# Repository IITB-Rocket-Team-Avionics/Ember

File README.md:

# Ember

Ember is the SRAD flight computer system of the IITB Rocket Team, developed as an experimental platform with mitigations for issues faced by previous systems and as a testbed for new avionics architecture.

## Version Descriptions

### Ember Pilot
Proof of concept version validating new LoRa telemetry and core sensor suite. Features a Raspberry Pi Pico 2 dev board instead of a bare-metal hardware design. All systems validated for future versions.

| Parameter | Details |
|-----------|---------|
| MCU | RP2350A (Pico 2 dev board) |
| Layers | 4 |
| Sensors | BMP280, BNO055, KX134 |
| GNSS | Teseo LIV3F |
| Telemetry | Waveshare Core SX1262 (920MHz LoRa) |

---

### Ember V0.2 (Ember)
First full flight version. Flew successfully at IREC 2026, reaching an apogee of 9,463 ft with a SRAD N-class KNSB motor — 2% overshoot on OpenRocket predicted apogee of 9,272 ft. Split into two boards: Flight Computer Unit (FCU) and Telemetry & Data Unit (TDU).

| Parameter | Details |
|-----------|---------|
| FCU MCU | RP2350A (Pico 2 dev board) |
| TDU MCU | RP2350A (Pico 2 dev board) |
| Layers | 2 |
| Sensors | BMP280, BNO055, KX134, NXP MPXV5100DP |
| GNSS | Quectel L89HA (multi-constellation) |
| Telemetry | Waveshare Core1262 SX1262 (920MHz LoRa) |
| Recovery | Dual deploy — drogue at apogee, main at 400m AGL |
| Pyro channels | 4 (2 primary, 2 redundant) |
| Data logging | External flash |
| COTS backup | EasyMini V2 |

---

### Ember V1 (In Development)
Major architectural redesign with full separation of concerns across dedicated board types. Introduces triple modular redundant recovery, distributed CAN bus architecture, and significantly upgraded data acquisition.

**Board types:**

**NTDU (Navigation, Telemetry & Data Unit)** — main board. Independent sensor suite for navigation and state estimation, GNSS, LoRa telemetry, data acquisition (dp probe, strain gauges), configuration authority for all nodes on boot, aggregates and logs data from all CAN nodes.

| Parameter | Details |
|-----------|---------|
| MCU | STM32H573 |
| Sensors | BMP384, BNO055, KX134, NXP MPXV5100DP (via ADS1220), BX350-3AA strain gauges (via ADS1220) |
| GNSS | Quectel L89HA |
| Telemetry | SX1262 920MHz LoRa |
| Data logging | OctoSPI NOR flash + microSD |
| Communication | CAN bus (all nodes) |
| Power | 2S Li-ion, AP63205WU buck (5V) |

**RU (Recovery Unit) — x3** — dedicated recovery boards in triple modular redundant configuration. Distributed 2-of-3 voting via CAN bus. Each board independently detects apogee and participates in consensus voting.

| Parameter | Details |
|-----------|---------|
| MCU | STM32F411 |
| Sensors | BMP280, single-axis accelerometer |
| Pyro channels | 2 (drogue + main) |
| Communication | CAN bus (shared with NTDU) |
| RTOS | FreeRTOS |
| Power | 1S Li-ion (isolated per board) |
| Voting | 2-of-3 mid-value select consensus |

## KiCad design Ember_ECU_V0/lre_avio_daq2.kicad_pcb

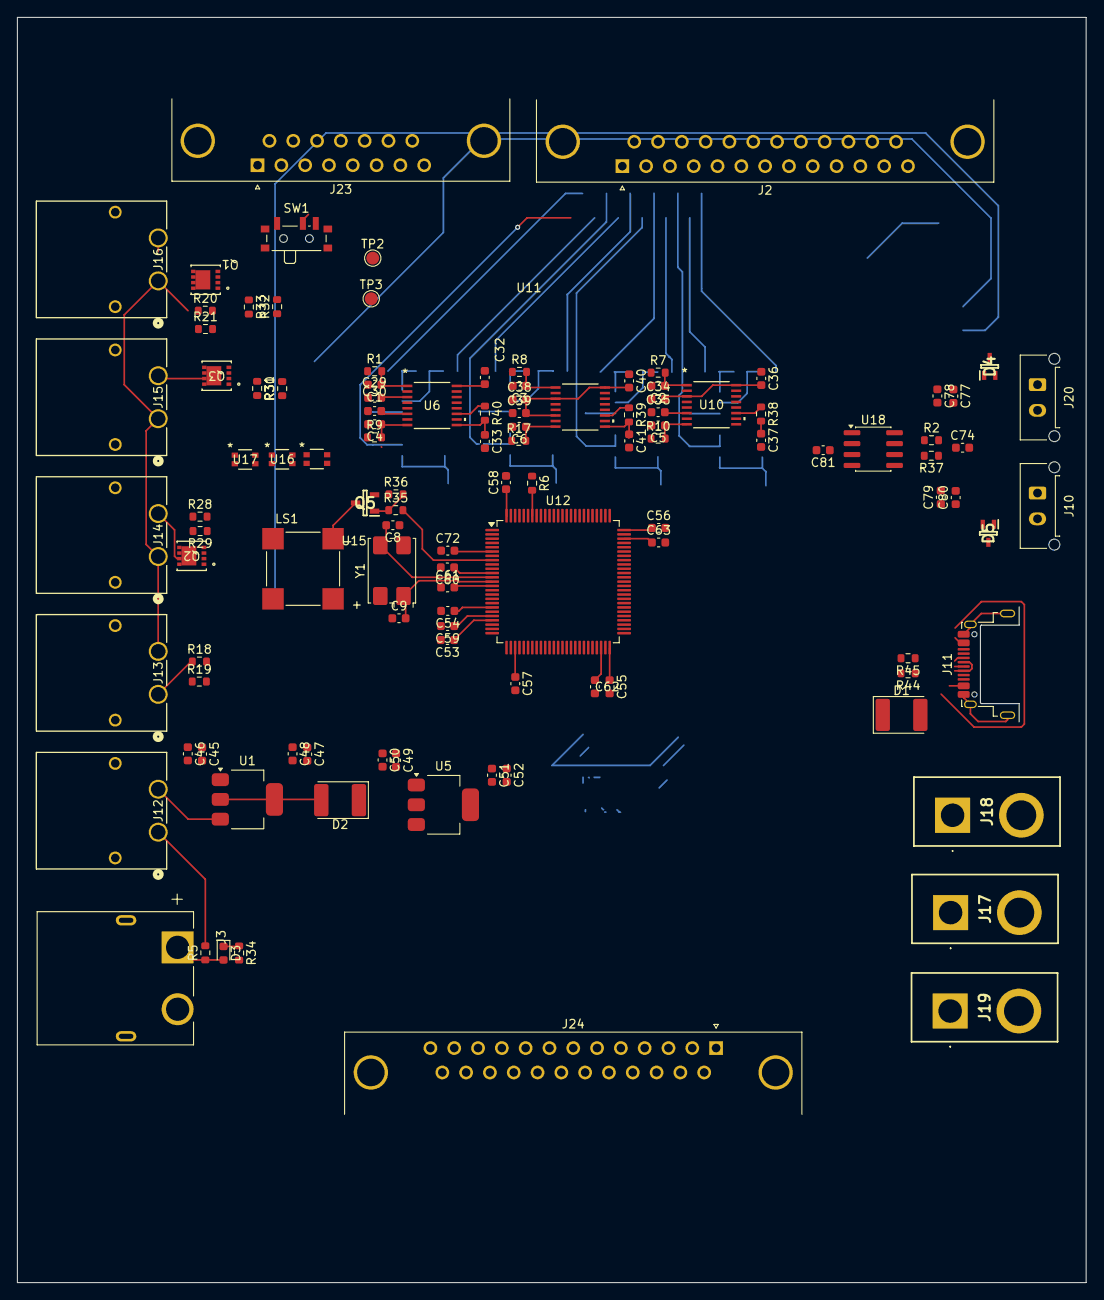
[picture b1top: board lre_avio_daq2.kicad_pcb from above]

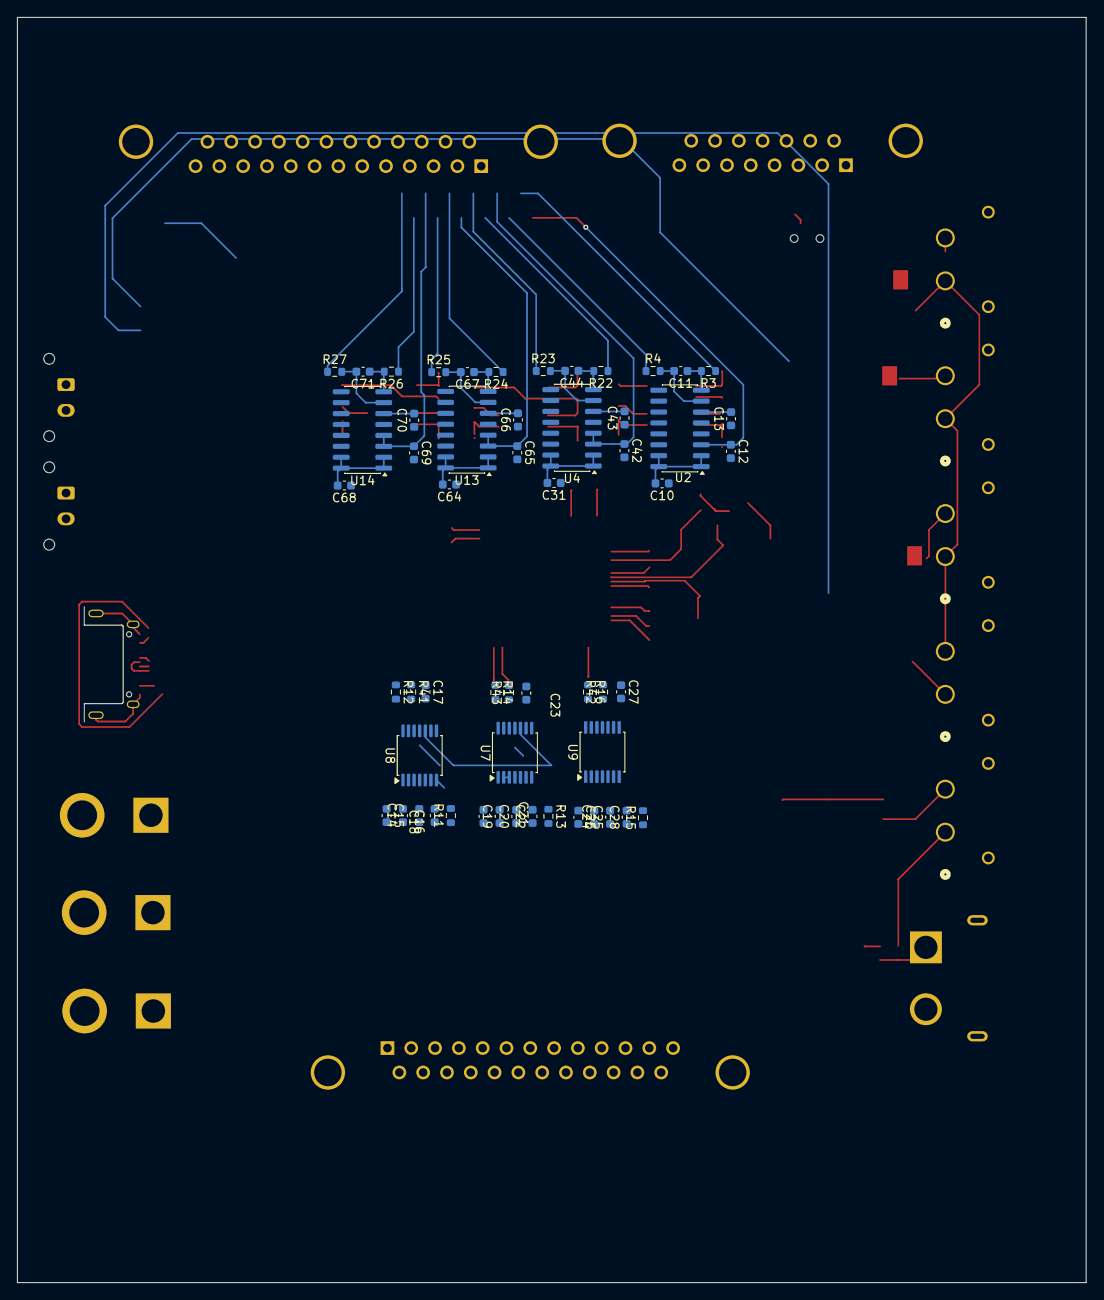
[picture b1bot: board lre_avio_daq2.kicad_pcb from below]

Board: 4 copper layers, 124.4 x 147.2 mm, 168 parts (55 on the bottom side), 125 nets.

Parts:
C1, C2, C3, C4, C5, C6: 1nF; C_0603_1608Metric
C8, C9: 20 pF; C_0603_1608Metric
C10, C12, C31, C42, C64, C65, C68, C69: 10 muF; C_0603_1608Metric
C11, C13, C14, C16, C17, C19, C22, C23, C24, C27, C28, C43, C44, C66, C67, C70, C71: 0.1 muF; C_0603_1608Metric
C15, C18, C20, C21, C25, C26: 0.01 muF; C_0603_1608Metric
C29, C30, C32, C33, C34, C35, C36, C37, C38, C39, C40, C41, C74: C; C_0603_1608Metric
C45, C47, C50, C51, C53, C54, C55, C56, C57, C58, C61, C72: 100 nF; C_0603_1608Metric
C46, C48, C49, C52, C60: 1 muF; C_0603_1608Metric
C59: 10 nF; C_0603_1608Metric
C62, C63: 4.7 muF; C_0603_1608Metric
C77, C78, C79, C80: 47pf; C_0603_1608Metric
C81: 100nF; C_0603_1608Metric
D1, D2: D_Schottky; D_2114_3652Metric
D3: LED; LED_0603_1608Metric
D4, D5: ESDCAN02-2BWY; SOT65P210X110-3N
J2, J24: DB25_Socket_MountingHoles; DSUB-25_Socket_Horizontal_P2.77x2.84mm_EdgePinOffset4.94mm_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
J3: XT60PW-M; AMASS_XT60PW-M
J10, J20: Conn_01x02_Pin; Molex_Micro-Fit_3.0_43650-0215_1x02_P3.00mm_Vertical
J11: USB_C_Receptacle_USB2.0_16P; USB_C_Receptacle_Amphenol_12401948E412A
J12, J13, J14, J15, J16: XT30PW-F; CONN_XT30PW-F_AMA
J17, J18, J19: SMPW-CC-K-M; SMPWCCKM
J23: DA15_Socket_MountingHoles; DSUB-15_Socket_Horizontal_P2.77x2.84mm_EdgePinOffset4.94mm_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
LS1: CMT-8530S-SMT; CUI_CMT-8530S-SMT
Q1, Q2, Q3: SISA96DN-T1-GE3; MOSFET_1DN-T1-GE3_VIS
Q5: SOT95P240X115-3N
R1, R3, R4, R7, R8, R9, R10, R17, R22, R23, R24, R25, R26, R27, R35: 100; R_0603_1608Metric
R2, R34, R37: R; R_0603_1608Metric
R5: RSX501LAM20TR; R_0603_1608Metric
R6, R11, R12, R13, R14, R15, R16, R41, R42, R43: 10K; R_0603_1608Metric
R18, R20: 150K; R_0603_1608Metric
R19, R21: 100K; R_0603_1608Metric
R28, R30, R32: 33k; R_0603_1608Metric
R29, R31, R33: 1k; R_0603_1608Metric
R36, R38, R39, R40: 10k; R_0603_1608Metric
R44, R45: 22; R_0603_1608Metric
SW1: SW_SPDT; SW_SPDT_PCM12
TP2, TP3: TestPoint_Probe; TestPoint_Pad_D1.5mm
U1, U5: AMS1117-5.0; SOT-223-3_TabPin2
U2, U4, U13, U14: HX711; SOIC-16_3.9x9.9mm_P1.27mm
U6, U10, U11: ADS8353QPWRQ1; TSSOP16_PW_TEX-L
U7, U8, U9: MAX31856; TSSOP-14_4.4x5mm_P0.65mm
U12: STM32F412VGTx; LQFP-100_14x14mm_P0.5mm
U15, U16, U17: WS2812B-2020; SMT_12B-2020_WDS
U18: TCAN330; SOIC-8_3.9x4.9mm_P1.27mm
Y1: Crystal_8Mhz; Crystal_SMD_7050-4Pin_7.0x5.0mm

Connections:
/3v3: C10.2, C16.2, C17.2, C22.2, C23.2, C27.2, C28.2, C31.2, C33.1, C37.1, C41.1, C51.2, C52.2, C53.1, C54.1, C55.1, C56.1, C57.1, C58.1, C59.1, C60.1, C64.2, C68.2, C72.2, C81.1, LS1.P, R11.1, R12.1, R13.1, R14.1, R15.1, R16.1, R38.2, R39.2, R40.2, R41.1, R42.1, R43.1, SW1.3 (C), U2.1 (VSUP), U2.2 (BASE), U2.15 (RATE), U2.16 (DVDD), U4.1 (VSUP), U4.2 (BASE), U4.15 (RATE), U4.16 (DVDD), U5.2 (VO), U6.9 (DVDD), U7.5 (AVDD), U7.8 (DVDD), U8.5 (AVDD), U8.8 (DVDD), U9.5 (AVDD), U9.8 (DVDD), U10.9 (DVDD), U11.9 (DVDD), U12.6 (VBAT), U12.11 (VDD), U12.19 (VDD), U12.21 (VREF+), U12.22 (VDDA), U12.28 (VDD), U12.50 (VDD), U12.75 (VDD), U12.100 (VDD), U13.1 (VSUP), U13.2 (BASE), U13.15 (RATE), U13.16 (DVDD), U14.1 (VSUP), U14.2 (BASE), U14.15 (RATE), U14.16 (DVDD), U18.3 (VCC)
/5v: C29.2, C30.2, C32.2, C34.2, C35.2, C36.2, C38.2, C39.2, C40.2, C47.2, C48.2, D1.1 (K), D2.2 (A), J2.8, J2.9, J2.10, J2.20, J2.21, J2.22, U1.2 (VO), U6.3 (REFIO_A), U6.6 (REFIO_B), U6.16 (AVDD), U10.3 (REFIO_A), U10.6 (REFIO_B), U10.16 (AVDD), U11.3 (REFIO_A), U11.6 (REFIO_B), U11.16 (AVDD), U15.4 (VDD), U16.4 (VDD), U17.4 (VDD)
/7v4: C45.2, C46.2, J12.2, J13.1, J24.11, J24.12, J24.13, J24.24, J24.25, R18.1, U1.3 (VI)
/7v4_DOUT: J12.1, R5.2
/ARM: R20.2, R21.1, U12.16 (PC1), U12.26 (PA3)
/BATTERY_MON: R18.2, R19.1, U12.24 (PA1)
/Buzzer_G: R35.2, U12.8 (PC14)
/CAN_N: C77.2, C80.2, D4.1 (A_1), J10.1, J20.1, R37.2, U18.6 (CANL)
/CAN_P: C78.2, C79.2, D4.2 (A_2), J10.2, J20.2, R2.1, U18.7 (CANH)
/CAN_RX: U12.81 (PD0), U18.4 (RXD)
/CAN_TX: U12.82 (PD1), U18.1 (TXD)
/Conn1: R29.1, U12.43 (PE12)
/Conn2: R31.1, U12.46 (PE15)
/Conn3: R33.1, U12.83 (PD2)
/DI1: U12.9 (PC15), U15.3 (DI)
/DI2: U15.1 (DO), U16.3 (DI)
/DI3: U16.1 (DO), U17.3 (DI)
/E+1: C12.1, J23.1, U2.3 (AVDD), U2.4 (VFB)
/E+2: C42.1, J23.10, U4.3 (AVDD), U4.4 (VFB)
/E+3: C65.1, J23.4, U13.3 (AVDD), U13.4 (VFB)
/E+4: C69.1, J23.13, U14.3 (AVDD), U14.4 (VFB)
/HX711_DOUT1: U2.12 (DOUT), U12.85 (PD4)
/HX711_DOUT2: U4.12 (DOUT), U12.86 (PD5)
/HX711_DOUT3: U12.87 (PD6), U13.12 (DOUT)
/HX711_DOUT4: U12.88 (PD7), U14.12 (DOUT)
/HX711_SCK: U2.11 (PD_SCK), U4.11 (PD_SCK), U12.33 (PC4), U13.11 (PD_SCK), U14.11 (PD_SCK)
/OSC_IN: C8.2, U12.12 (PH0), Y1.3
/OSC_OUT: C9.2, U12.13 (PH1), Y1.1
/PWM_SERVO1: J24.1, J24.14, U12.40 (PE9)
/PWM_SERVO2: J24.2, J24.15, U12.42 (PE11)
/PWM_SERVO3: J24.3, J24.16, U12.44 (PE13)
/PWM_SERVO4: J24.4, J24.17, U12.45 (PE14)
/PWM_SERVO5: J24.5, J24.18, U12.23 (PA0)
/PWM_SERVO6: J24.6, J24.19, U12.89 (PB3)
/PWM_SERVO7: J24.7, J24.20, U12.25 (PA2)
/S+1: J23.9, R3.1
/S+2: J23.3, R22.1
/S+3: J23.12, R24.1
/S+4: J23.6, R26.1
/S-1: J23.2, R4.1
/S-2: J23.11 (P111), R23.1
/S-3: J23.5, R25.1
/S-4: J23.14, R27.1
/SPI1_MISO: U7.11 (SDO), U8.11 (SDO), U9.11 (SDO), U12.31 (PA6)
/SPI1_MOSI: U7.12 (SDI), U8.12 (SDI), U9.12 (SDI), U12.32 (PA7)
/SPI1_SCK: U7.10 (SCK), U8.10 (SCK), U9.10 (SCK), U12.30 (PA5)
/SPI2_CS: R40.1, U6.11 (*CS), U12.51 (PB12)
/SPI2_MISO: U6.12 (SCLK), U12.17 (PC2)
/SPI2_MOSI: U6.10 (SDI), U12.18 (PC3)
/SPI2_SCK: U6.13 (SDO_A), U12.52 (PB13)
/SPI3_CS: R38.1, U10.11 (*CS), U12.77 (PA15)
/SPI3_MISO: U10.12 (SCLK), U12.79 (PC11)
/SPI3_MOSI: U10.10 (SDI), U12.80 (PC12)
/SPI3_SCK: U10.13 (SDO_A), U12.78 (PC10)
/SPI4_CS: R39.1, U11.11 (*CS), U12.3 (PE4)
/SPI4_MISO: U11.12 (SCLK), U12.4 (PE5)
/SPI4_MOSI: U11.10 (SDI), U12.5 (PE6)
/SPI4_SCK: U11.13 (SDO_A), U12.1 (PE2)
/TC1_CS: R43.2, U7.9 (~CS), U12.29 (PA4)
/TC2_CS: R41.2, U8.9 (~CS), U12.35 (PB0)
/TC3_CS: R42.2, U9.9 (~CS), U12.36 (PB1)
/USB_D+: J11.A7 (D-), J11.B7 (D-), R44.1
/USB_D-: J11.A6 (D+), J11.B6 (D+), R45.1
/USB_DN: R44.2, U12.70 (PA11)
/USB_DP: R45.2, U12.71 (PA12)
/V_BATT: D3.2 (A), J3.1, R5.1
/pt1: J2.1, J2.14, R1.1
/pt2: J2.2, J2.15, R9.1
/pt3: J2.3, J2.16, R7.1
/pt4: J2.4, J2.17, R10.1
/pt5: J2.5, J2.18, R8.1
/pt6: J2.6, J2.19, R17.1
GND: C1.2, C2.2, C3.2, C4.2, C5.2, C6.2, C8.1, C9.1, C10.1, C12.2, C13.1, C15.2, C16.1, C17.1, C18.1, C20.1, C21.2, C22.1, C23.1, C25.1, C26.2, C27.1, C28.1, C29.1, C30.1, C31.1, C32.1, C33.2, C34.1, C35.1, C36.1, C37.2, C38.1, C39.1, C40.1, C41.2, C42.2, C43.1, C45.1, C46.1, C47.1, C48.1, C49.1, C50.1, C51.1, C52.1, C53.2, C54.2, C55.2, C56.2, C57.2, C58.2, C59.2, C60.2, C62.2, C63.2, C64.1, C65.2, C66.1, C68.1, C69.2, C70.2, C72.1, C74.2, C77.1, C78.1, C79.1, C80.1, C81.2, D4.3 (A_3), D5.3 (A_3), J2.11, J2.12, J2.13, J2.24, J2.25, J2.SH (PAD), J3.2 (N), J3.SH1 (SHIELD), J3.SH2 (SHIELD), J11.A1 (GND), J11.A12 (GND), J11.B1 (GND), J11.B12 (GND), J11.SH (SHIELD), J23.7, J23.8, J23.15, J23.SH (PAD), J24.9, J24.10, J24.21, J24.22, J24.SH (PAD), Q1.1 (S_1), Q1.2 (S_2), Q1.3 (S_3), Q2.1 (S_1), Q2.2 (S_2), Q2.3 (S_3), Q3.1 (S_1), Q3.2 (S_2), Q3.3 (S_3), Q5.2 (S), R19.2, R21.2, R28.2, R30.2, R32.2, R34.2, R36.1, SW1.1 (A), TP3.1 (1_1), U1.1 (GND), U2.5 (AGND), U4.5 (AGND), U5.1 (GND), U6.2 (AINM_A), U6.4 (REFGND_A), U6.5 (REFGND_B), U6.7 (AINM_B), U6.15 (GND), U7.1 (AGND), U7.14 (DGND), U8.1 (AGND), U8.14 (DGND), U9.1 (AGND), U9.14 (DGND), U10.2 (AINM_A), U10.4 (REFGND_A), U10.5 (REFGND_B), U10.7 (AINM_B), U10.15 (GND), U11.2 (AINM_A), U11.4 (REFGND_A), U11.5 (REFGND_B), U11.7 (AINM_B), U11.15 (GND), U12.10 (VSS), U12.20 (VSSA), U12.27 (VSS), U12.49 (VSS), U12.74 (VSS), U12.99 (VSS), U13.5 (AGND), U14.5 (AGND), U15.2 (GND), U16.2 (GND), U17.2 (GND), U18.2 (GND), U18.5 (SHDN), U18.8 (S), Y1.2, Y1.4
unnamed: C61.1, TP2.1 (1_1)
unnamed: C74.1, R2.2, R37.1
unnamed: D1.2 (A), J11.A4 (VBUS), J11.A9 (VBUS), J11.B4 (VBUS), J11.B9 (VBUS)
unnamed: C49.2, C50.2, D2.1 (K), U5.3 (VI)
unnamed: D3.1 (K), R34.1
unnamed: J13.2, J14.1, J15.1, J16.1, R20.1
unnamed: C19.1, C20.2, J17.1 (+), U7.4 (T+)
unnamed: C19.2, C21.1, J17.2 (-), U7.2 (BIAS), U7.3 (T-)
unnamed: C14.1, C18.2, J18.1 (+), U8.4 (T+)
unnamed: C14.2, C15.1, J18.2 (-), U8.2 (BIAS), U8.3 (T-)
unnamed: C24.1, C25.2, J19.1 (+), U9.4 (T+)
unnamed: C24.2, C26.1, J19.2 (-), U9.2 (BIAS), U9.3 (T-)
unnamed: Q1.5 (D_1), Q1.6 (D_2)
unnamed: J16.2, Q1.7 (D_3), Q1.8 (D_4)
unnamed: Q1.4 (G), R32.1, R33.2
unnamed: Q2.5 (D_1), Q2.6 (D_2)
unnamed: J14.2, Q2.7 (D_3), Q2.8 (D_4)
unnamed: Q2.4 (G), R28.1, R29.2
unnamed: Q3.5 (D_1), Q3.6 (D_2)
unnamed: J15.2, Q3.7 (D_3), Q3.8 (D_4)
unnamed: Q3.4 (G), R30.1, R31.2
unnamed: LS1.N, Q5.3 (D)
unnamed: Q5.1 (G), R35.1, R36.2
unnamed: R6.1, SW1.2 (B)
unnamed: C11.1, R3.2, U2.8 (INA+)
unnamed: C11.2, R4.2, U2.7 (INA-)
unnamed: C13.2, U2.6 (VBG)
unnamed: C44.1, R22.2, U4.8 (INA+)
unnamed: C44.2, R23.2, U4.7 (INA-)
unnamed: C43.2, U4.6 (VBG)
unnamed: C1.1, R1.2, U6.1 (AINP_A)
unnamed: C4.1, R9.2, U6.8 (AINP_B)
unnamed: R13.2, U7.7 (~DRDY)
unnamed: R14.2, U7.13 (~FAULT)
unnamed: R11.2, U8.7 (~DRDY)
unnamed: R12.2, U8.13 (~FAULT)
unnamed: R15.2, U9.7 (~DRDY)
unnamed: R16.2, U9.13 (~FAULT)
unnamed: C2.1, R7.2, U10.1 (AINP_A)
unnamed: C5.1, R10.2, U10.8 (AINP_B)
unnamed: C3.1, R8.2, U11.1 (AINP_A)
unnamed: C6.1, R17.2, U11.8 (AINP_B)
unnamed: R6.2, U12.94 (BOOT0)
unnamed: C61.2, U12.14 (NRST)
unnamed: C62.1, U12.48 (VCAP_1)
unnamed: C63.1, U12.73 (VCAP_2)
unnamed: C67.1, R24.2, U13.8 (INA+)
unnamed: C67.2, R25.2, U13.7 (INA-)
unnamed: C66.2, U13.6 (VBG)
unnamed: C71.1, R26.2, U14.8 (INA+)
unnamed: C71.2, R27.2, U14.7 (INA-)
unnamed: C70.1, U14.6 (VBG)

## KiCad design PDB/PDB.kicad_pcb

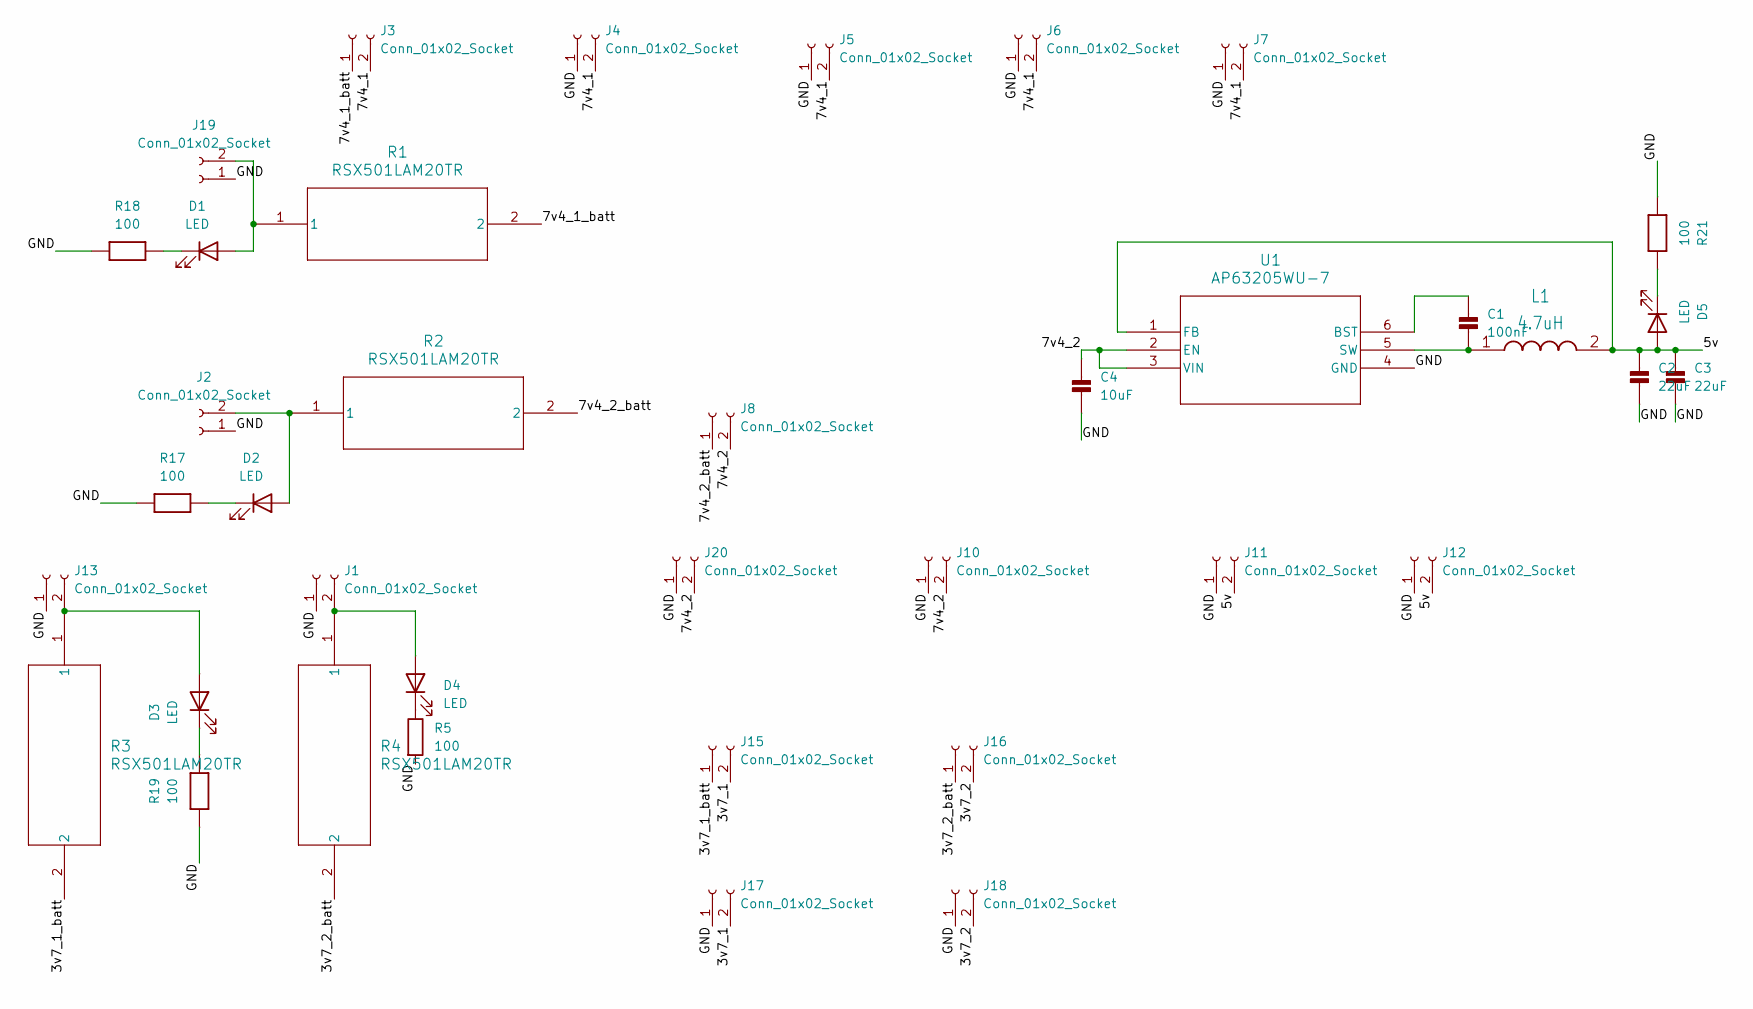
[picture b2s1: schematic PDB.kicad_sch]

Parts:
C1: 100nF; C_0603_1608Metric
C2, C3: 22uF; C_0603_1608Metric
C4: 10uF; C_0603_1608Metric
D1, D2, D3, D4, D5: LED; LED_0603_1608Metric
J1, J3, J4, J5, J6, J7, J8, J10, J11, J12, J13, J15, J16, J17, J18, J20: Conn_01x02_Socket; AMASS_XT30PW-M_1x02_P2.50mm_Horizontal
J2, J19: Conn_01x02_Socket; AMASS_XT60PW-M_1x02_P7.20mm_Horizontal
L1: 4.7uH; L_Neosid_SMS-ME3015
R1, R2, R3, R4: RSX501LAM20TR; DIO_RB050LAM_ROM
R5, R17, R18, R19, R21: 100; R_0603_1608Metric
U1: AP63205WU-7; SOIC_05WU-7_DIO

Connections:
/3v7_1: J15.2, J17.2
/3v7_1_batt: J15.1, R3.2
/3v7_2: J16.2, J18.2
/3v7_2_batt: J16.1, R4.2
/5v: C2.1, C3.1, D5.2 (A), J11.2, J12.2, L1.2, U1.1 (FB)
/7v4_1: J3.2, J4.2, J5.2, J6.2, J7.2
/7v4_1_batt: J3.1, R1.2
/7v4_2: C4.1, J8.2, J10.2, J20.2, U1.2 (EN), U1.3 (VIN)
/7v4_2_batt: J8.1, R2.2
/GND: C2.2, C3.2, C4.2, J1.1, J2.1, J4.1, J5.1, J6.1, J7.1, J10.1, J11.1, J12.1, J13.1, J17.1, J18.1, J19.1, J20.1, R5.2, R17.1, R18.1, R19.1, R21.1, U1.4 (GND)
unnamed: C1.1, U1.6 (BST)
unnamed: C1.2, L1.1, U1.5 (SW)
unnamed: D1.2 (A), J19.2, R1.1
unnamed: D1.1 (K), R18.2
unnamed: D2.2 (A), J2.2, R2.1
unnamed: D2.1 (K), R17.2
unnamed: D3.2 (A), J13.2, R3.1
unnamed: D3.1 (K), R19.2
unnamed: D4.2 (A), J1.2, R4.1
unnamed: D4.1 (K), R5.1
unnamed: D5.1 (K), R21.2

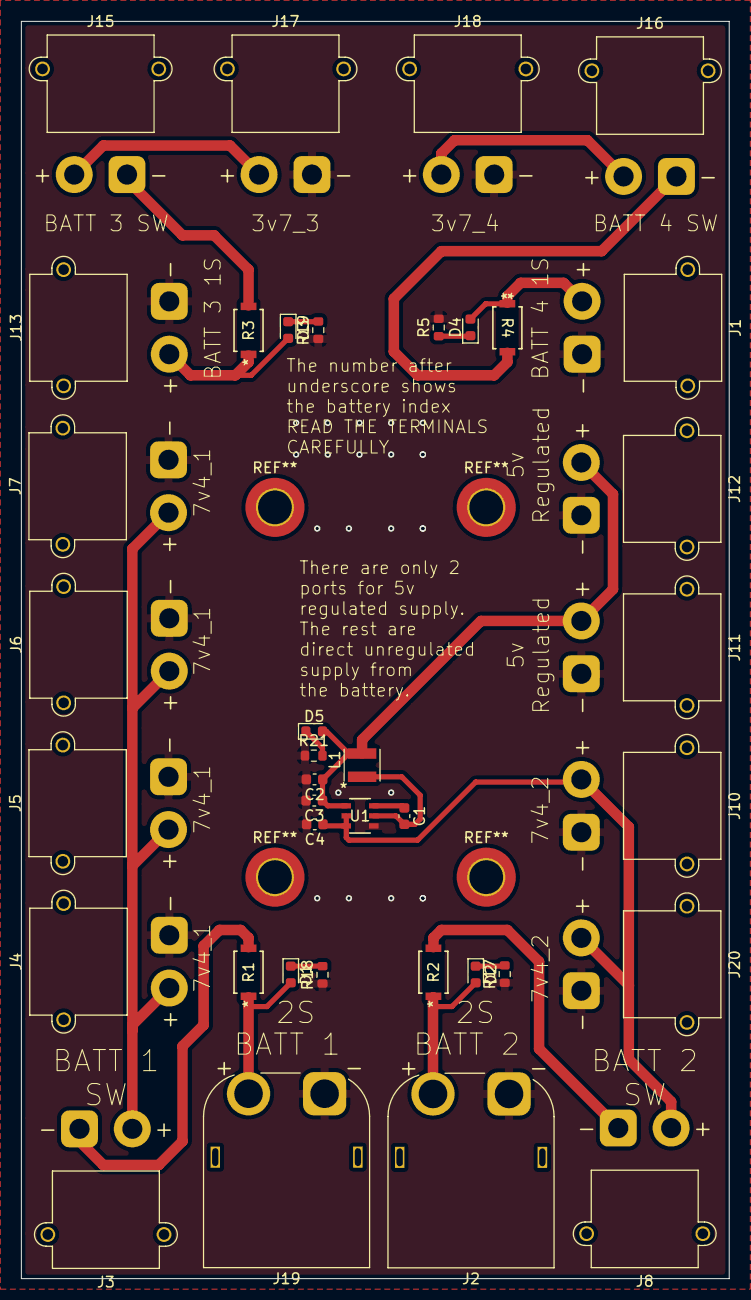
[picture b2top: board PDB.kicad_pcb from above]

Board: 2 copper layers, 67.0 x 119.0 mm, 38 parts (0 on the bottom side), 21 nets.

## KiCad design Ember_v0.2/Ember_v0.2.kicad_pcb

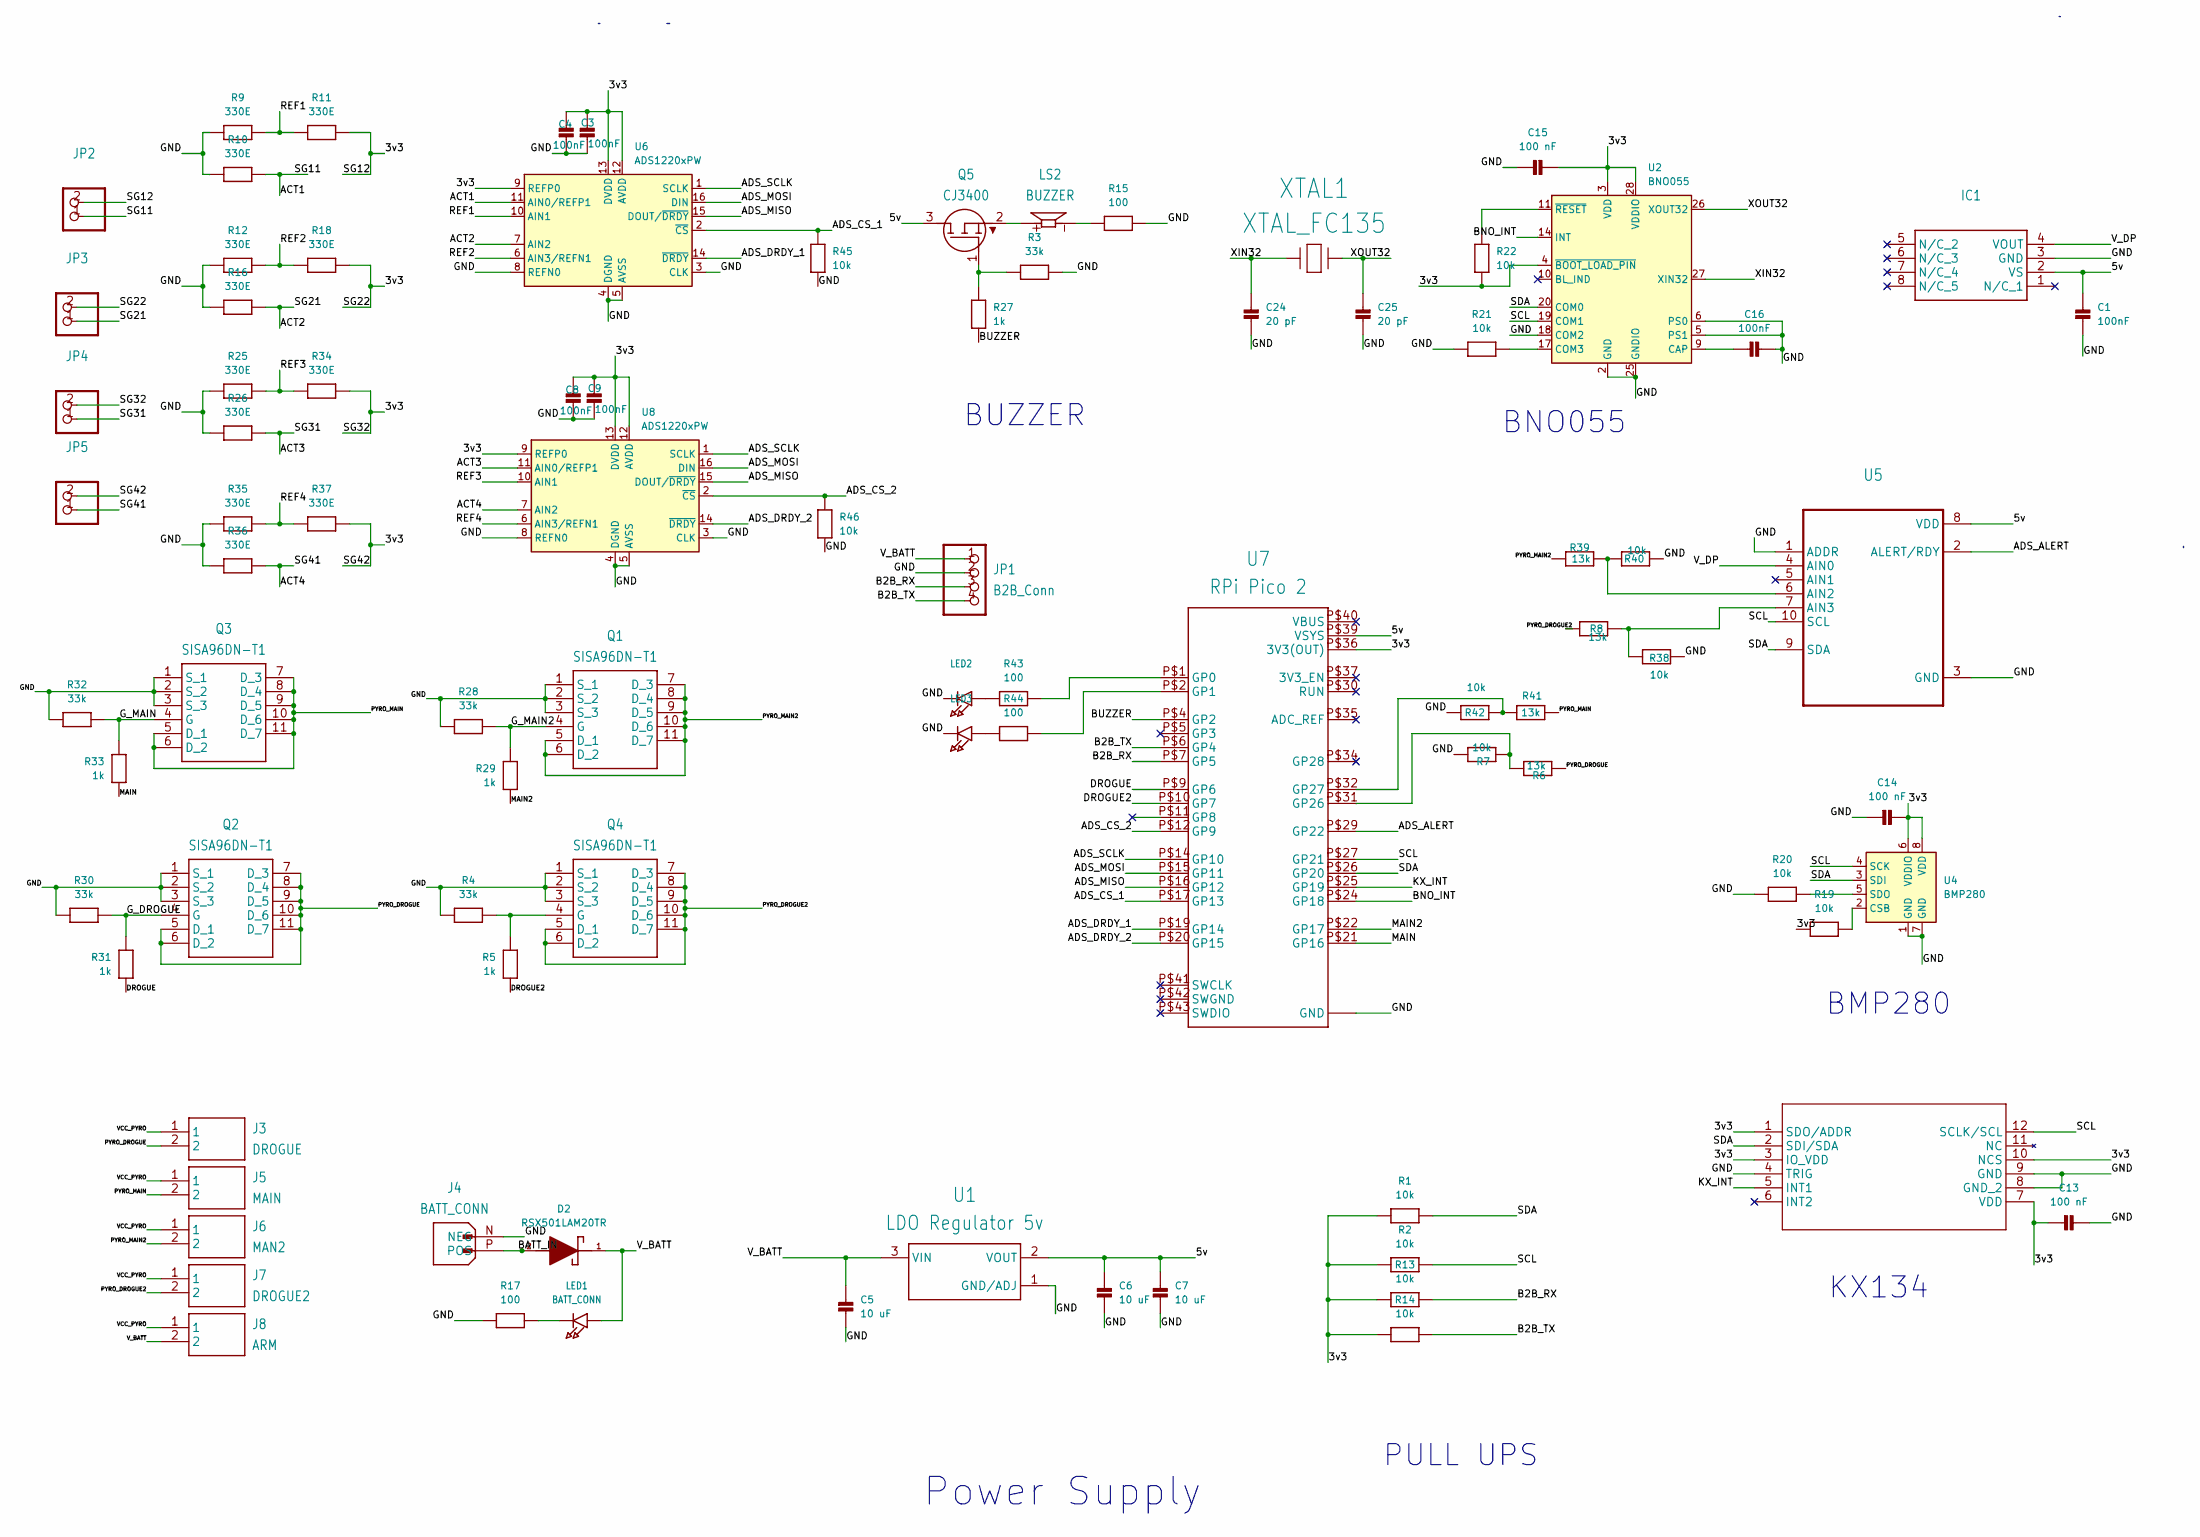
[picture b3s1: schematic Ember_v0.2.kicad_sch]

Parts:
C1, C3, C4, C8, C9, C16: 100nF; 0603
C5, C6, C7: 10 uF; 0603
C13, C14, C15: 100 nF; 0603
C24, C25: 20 pF; 0603
D2: RSX501LAM20TR; DIOM4725X105N; MOUSER_PART_NUMBER 755-RSX501LAM20TR; DigiKey_Part_Number RSX501LAM20CT-ND
IC1: MPXV5100DP
J3: DROGUE; ONSHORE_OSTTA020161
J4: BATT_CONN; AMASS_XT60-M
J5: MAIN; ONSHORE_OSTTA020161
J6: MAN2; ONSHORE_OSTTA020161
J7: DROGUE2; ONSHORE_OSTTA020161
J8: ARM; ONSHORE_OSTTA020161
JP1: B2B_Conn; 1X04_OVAL
JP2, JP3, JP4, JP5: 1X02_OVAL
LED1: BATT_CONN; CHIPLED_0603
LED2, LED3: CHIPLED_0603
LS2: BUZZER; CUI_CMT-8530S-SMT
Q1, Q2, Q3, Q4: SISA96DN-T1; SIS862DNT1GE3
Q5: CJ3400; SOT95P240X115-3N
R1, R2, R7, R13, R14, R19, R20, R21, R22, R38, R40, R42, R45, R46: 10k; 0603
R3, R4, R28, R30, R32: 33k; 0603
R5, R27, R29, R31, R33: 1k; 0603
R6, R8, R39, R41: 13k; 0603
R9, R10, R11, R12, R16, R18, R25, R26, R34, R35, R36, R37: 330E; 0603
R15, R17, R43, R44: 100; 0603
U1: LDO Regulator 5v; SOT229P700X180-4N
U2: BNO055; LGA-28_5.2x3.8mm_P0.5mm
U3: LGA12_2X2X0P9_ROM
U4: BMP280; Bosch_LGA-8_2x2.5mm_P0.65mm_ClockwisePinNumbering
U5: SOP50P490X110-10N
U6, U8: ADS1220xPW; TSSOP-16_4.4x5mm_P0.65mm
U7: RPi Pico 2; PICO-PKG-SMD
XTAL1: XTAL_FC135; XTAL_FC-135_EPS

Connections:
/3v3: C3.1, C4.1, C8.1, C9.1, C13.2, C14.1, C15.1, JP2.2, JP3.2, JP4.2, JP5.2, R1.1, R2.1, R11.2, R13.1, R14.1, R18.2, R19.1, R22.1, R34.2, R37.2, U2.3 (VDD), U2.4 (~BOOT_LOAD_PIN), U2.28 (VDDIO), U3.1 (SDO/ADDR), U3.3 (IO_VDD), U3.7 (VDD), U3.10 (NCS), U4.6 (VDDIO), U4.8 (VDD), U6.9 (REFP0), U6.12 (AVDD), U6.13 (DVDD), U7.P$36 (3V3(OUT)), U8.9 (REFP0), U8.12 (AVDD), U8.13 (DVDD)
/5v: C1.1, C6.1, C7.1, IC1.2 (VS), Q5.3 (D), U1.2 (VOUT), U5.8 (VDD), U7.P$39 (VSYS)
/ACT1: JP2.1, R10.2, U6.11 (AIN0/REFP1)
/ACT2: JP3.1, R16.2, U6.7 (AIN2)
/ACT3: JP4.1, R26.2, U8.11 (AIN0/REFP1)
/ACT4: JP5.1, R36.2, U8.7 (AIN2)
/ADS_ALERT: U5.2 (ALERT/RDY), U7.P$29 (GP22)
/ADS_CS_1: R45.1, U6.2 (~CS), U7.P$17 (GP13)
/ADS_CS_2: R46.1, U7.P$12 (GP9), U8.2 (~CS)
/ADS_DRDY_1: U6.14 (~DRDY), U7.P$19 (GP14)
/ADS_DRDY_2: U7.P$20 (GP15), U8.14 (~DRDY)
/ADS_MISO: U6.15 (DOUT/~DRDY), U7.P$16 (GP12), U8.15 (DOUT/~DRDY)
/ADS_MOSI: U6.16 (DIN), U7.P$15 (GP11), U8.16 (DIN)
/ADS_SCLK: U6.1 (SCLK), U7.P$14 (GP10), U8.1 (SCLK)
/B2B_RX: JP1.3, R13.2, U7.P$7 (GP5)
/B2B_TX: JP1.4, R14.2, U7.P$6 (GP4)
/BATT_IN: D2.2, J4.P (POS)
/BNO_INT: U2.14 (INT), U7.P$24 (GP18)
/BUZZER: R27.1, U7.P$4 (GP2)
/DROGUE: R31.1, U7.P$9 (GP6)
/DROGUE2: R5.1, U7.P$10 (GP7)
/GND: C1.2, C3.2, C4.2, C5.2, C6.2, C7.2, C8.2, C9.2, C13.1, C14.2, C15.2, C16.1, C24.1, C25.1, IC1.3 (GND), J4.N (NEG), JP1.2, LED2.C, LED3.C, Q1.1 (S_1), Q1.2 (S_2), Q1.3 (S_3), Q2.1 (S_1), Q2.2 (S_2), Q2.3 (S_3), Q3.1 (S_1), Q3.2 (S_2), Q3.3 (S_3), Q4.1 (S_1), Q4.2 (S_2), Q4.3 (S_3), R3.2, R4.2, R7.2, R9.1, R10.1, R12.1, R15.2, R16.1, R17.1, R20.1, R21.1, R25.1, R26.1, R28.2, R30.2, R32.2, R35.1, R36.1, R38.2, R40.2, R42.2, R45.2, R46.2, U1.1 (GND/ADJ), U2.2 (GND), U2.5 (PS1), U2.6 (PS0), U2.18 (COM2), U2.25 (GNDIO), U3.4 (TRIG), U3.8 (GND_2), U3.9 (GND), U4.1 (GND), U4.7 (GND), U5.1 (ADDR), U5.3 (GND), U6.3 (CLK), U6.4 (DGND), U6.5 (AVSS), U6.8 (REFN0), U7.P$3 (GND), U7.P$8 (GND), U7.P$13 (GND), U7.P$18 (GND), U7.P$23 (GND), U7.P$28 (GND), U7.P$33 (GND), U7.P$38 (GND), U8.3 (CLK), U8.4 (DGND), U8.5 (AVSS), U8.8 (REFN0)
/G_DROGUE: Q2.4 (G), R30.1, R31.2
/G_MAIN: Q3.4 (G), R32.1, R33.2
/G_MAIN2: Q1.4 (G), R28.1, R29.2
/KX_INT: U3.5 (INT1), U7.P$25 (GP19)
/MAIN: R33.1, U7.P$21 (GP16)
/MAIN2: R29.1, U7.P$22 (GP17)
/PYRO_DROGUE: J3.2, Q2.5 (D_1), Q2.6 (D_2), Q2.7 (D_3), Q2.8 (D_4), Q2.9 (D_5), Q2.10 (D_6), Q2.11 (D_7), R6.1
/PYRO_DROGUE2: J7.2, Q4.5 (D_1), Q4.6 (D_2), Q4.7 (D_3), Q4.8 (D_4), Q4.9 (D_5), Q4.10 (D_6), Q4.11 (D_7), R8.1
/PYRO_MAIN: J5.2, Q3.5 (D_1), Q3.6 (D_2), Q3.7 (D_3), Q3.8 (D_4), Q3.9 (D_5), Q3.10 (D_6), Q3.11 (D_7), R41.1
/PYRO_MAIN2: J6.2, Q1.5 (D_1), Q1.6 (D_2), Q1.7 (D_3), Q1.8 (D_4), Q1.9 (D_5), Q1.10 (D_6), Q1.11 (D_7), R39.1
/REF1: R9.2, R11.1, U6.10 (AIN1)
/REF2: R12.2, R18.1, U6.6 (AIN3/REFN1)
/REF3: R25.2, R34.1, U8.10 (AIN1)
/REF4: R35.2, R37.1, U8.6 (AIN3/REFN1)
/SCL: R2.2, U2.19 (COM1), U3.12 (SCLK/SCL), U4.4 (SCK), U5.10 (SCL), U7.P$27 (GP21)
/SDA: R1.2, U2.20 (COM0), U3.2 (SDI/SDA), U4.3 (SDI), U5.9 (SDA), U7.P$26 (GP20)
/VCC_PYRO: J3.1, J5.1, J6.1, J7.1, J8.1
/V_BATT: C5.1, D2.1, J8.2, JP1.1, LED1.A, U1.3 (VIN)
/V_DP: IC1.4 (VOUT), U5.4 (AIN0)
/XIN32: C24.2, U2.27 (XIN32), XTAL1.1
/XOUT32: C25.2, U2.26 (XOUT32), XTAL1.2
unnamed: C16.2, U2.9 (CAP)
unnamed: LED1.C, R17.2
unnamed: LED2.A, R43.1
unnamed: LED3.A, R44.1
unnamed: LS2.N, R15.1
unnamed: Q4.4 (G), R4.1, R5.2
unnamed: Q5.1 (G), R3.1, R27.2
unnamed: LS2.P, Q5.2 (S)
unnamed: R21.2, U2.17 (COM3)
unnamed: R22.2, U2.11 (~RESET)
unnamed: R19.2, U4.2 (CSB)
unnamed: R20.2, U4.5 (SDO)
unnamed: R39.2, R40.1, U5.6 (AIN2)
unnamed: R8.2, R38.1, U5.7 (AIN3)
unnamed: R43.2, U7.P$1 (GP0)
unnamed: R44.2, U7.P$2 (GP1)
unnamed: R6.2, R7.1, U7.P$31 (GP26)
unnamed: R41.2, R42.1, U7.P$32 (GP27)

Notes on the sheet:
KX134
BNO055
Power Supply
BUZZER
PULL UPS
BMP280

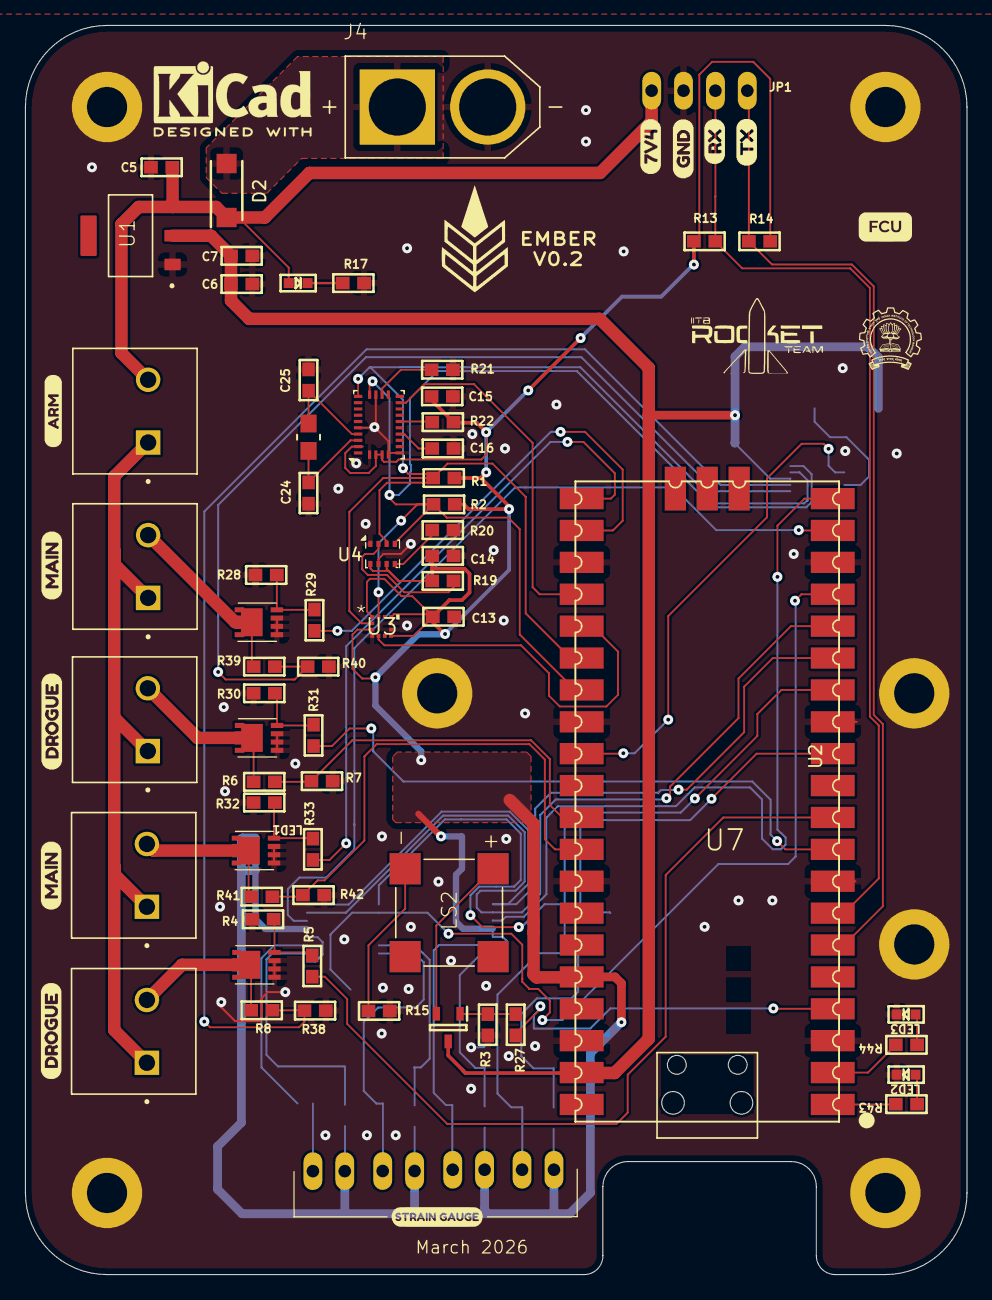
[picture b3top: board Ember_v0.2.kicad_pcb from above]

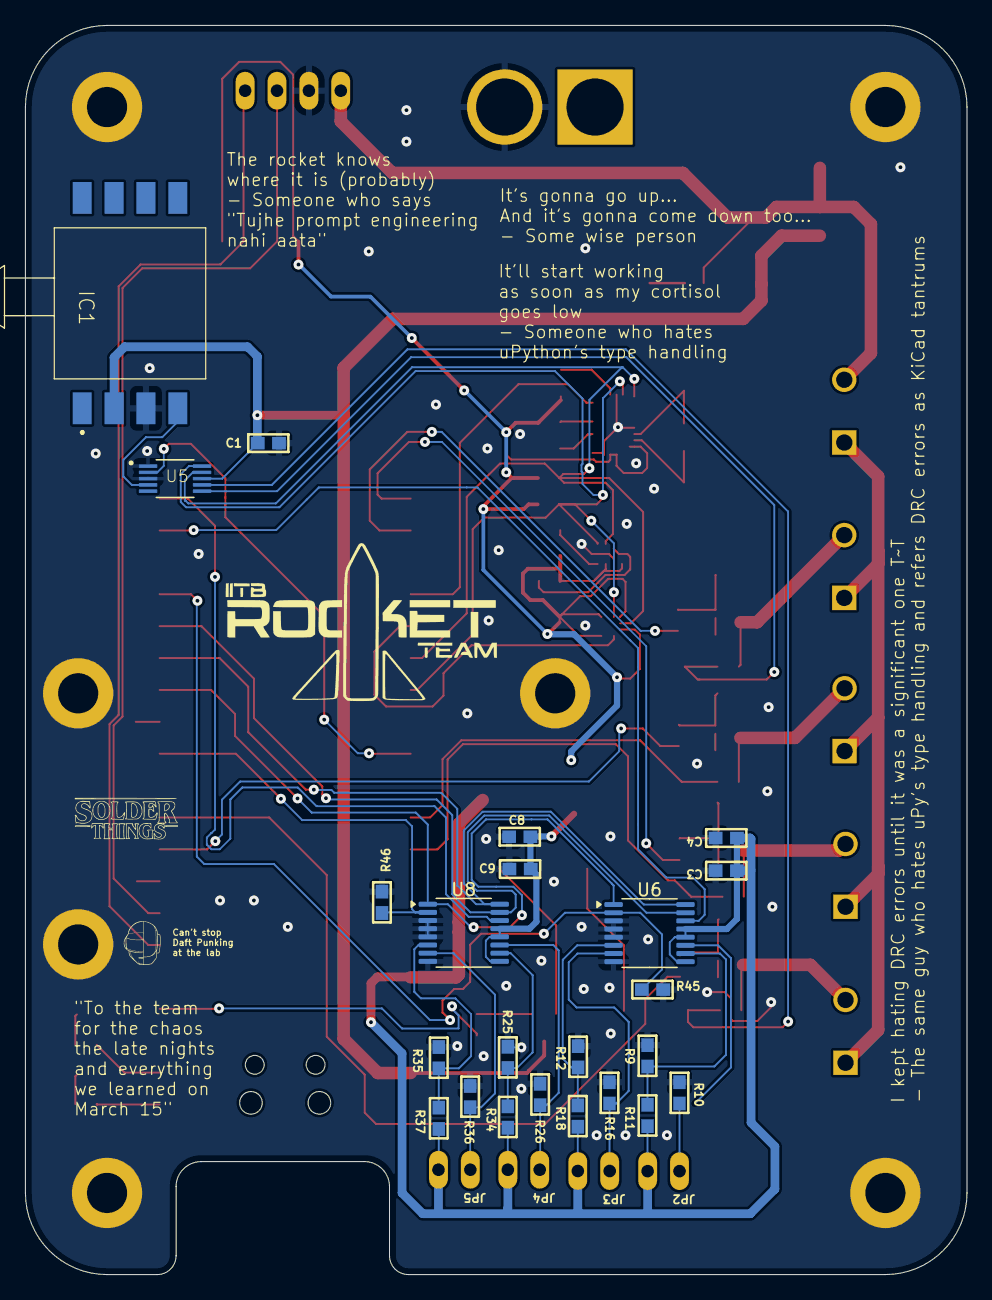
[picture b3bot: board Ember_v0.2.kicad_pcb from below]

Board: 2 copper layers, 75.0 x 99.5 mm, 89 parts (27 on the bottom side), 61 nets.
